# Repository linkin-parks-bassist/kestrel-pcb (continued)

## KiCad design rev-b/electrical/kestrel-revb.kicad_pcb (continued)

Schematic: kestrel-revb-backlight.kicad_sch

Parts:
C901: 4.7uF; C_0805_2012Metric; Rating 4.7uF / 25V X7R / input local
C902: 100nF; C_0603_1608Metric; Rating 100nF / 16V X7R / VIN bypass
C903: 2.2uF; C_1210_3225Metric; Rating 2.2uF / 50V X7R / effective >=1uF at 39V
C904: 100nF; C_0603_1608Metric; Rating 100nF / 16V X7R / buffer bypass
C905, C906: 4.7uF; C_0805_2012Metric; Rating 4.7uF / 16V X7R / effective >=1uF / LCD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
C907: 10pF; C_0603_1608Metric; Rating 10pF / 25V C0G / LCD feedforward
C908, C909: 4.7uF; C_0805_2012Metric; Rating 4.7uF / 16V X7R / effective >=1uF / tou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
C910: 10pF; C_0603_1608Metric; Rating 10pF / 25V C0G / touch feedforward
D901: SS16-E3/61T; D_SMA
L901: 10uH; L_Sunlord_MWSA0603S; Rating 10uH / shielded / Isat >=3A / MPN and l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
R901: 5.62ohm; R_0805_2012Metric; Rating 5.62ohm / 1% / >=0.125W / Kelvin sense
R902: 10k; R_0603_1608Metric; Rating 10k / 1% / MCU PWM default off
R903: 1k; R_0603_1608Metric; Rating 1k / 1% / control series
R904: 1M; R_1206_3216Metric; Rating 1M / 1% / 1206 / output bleed
R905: 100k; R_0603_1608Metric; Rating 100k / 1% / CTRL default off
R906: 33.2k; R_0603_1608Metric; Rating 33.2k / 0.1% / LCD upper feedback
R907: 10k; R_0603_1608Metric; Rating 10k / 0.1% / LCD lower feedback
R908: 30k; R_0603_1608Metric; Rating 30k / 0.1% / touch upper feedback
R909: 10k; R_0603_1608Metric; Rating 10k / 0.1% / touch lower feedback
TP901: BL_LED_A; TestPoint_Pad_D1.0mm
TP902: BL_LED_K; TestPoint_Pad_D1.0mm
TP903: LCD_VDD; TestPoint_Pad_D1.0mm
TP904: TOUCH_VDD; TestPoint_Pad_D1.0mm
U901: TPS61169DCKR; Texas_R-PDSO-G5_DCK-5
U902: SN74LVC1G125DCKR; Texas_R-PDSO-G5_DCK-5
U903, U904: TLV76701DRVR; WSON-6-1EP_2x2mm_P0.65mm_EP1x1.6mm_ThermalVias

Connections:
/+5V_DIG: C901.1, C902.1, C904.1, C905.1, C908.1, L901.1, U901.5 (VIN), U902.5 (VCC), U903.4 (EN), U903.6 (IN), U904.4 (EN), U904.6 (IN); also elsewhere on the board
/BL_LED_A: C903.1, D901.1 (K), R904.1, TP901.1; also elsewhere on the board
/BL_LED_K: R901.1, TP902.1, U901.3 (FB); also elsewhere on the board
/Backlight and display supplies/BL_CTRL: R903.2, R905.1, U901.4 (CTRL)
/Backlight and display supplies/BL_CTRL_BUFFER: R903.1, U902.4
/Backlight and display supplies/BL_SW: D901.2 (A), L901.2, U901.1 (SW)
/Backlight and display supplies/LCD_FB: C907.2, R906.2, R907.1, U903.2 (FB)
/Backlight and display supplies/TOUCH_FB: C910.2, R908.2, R909.1, U904.2 (FB)
/GND: C901.2, C902.2, C903.2, C904.2, C905.2, C906.2, C908.2, C909.2, R901.2, R902.2, R904.2, R905.2, R907.2, R909.2, U901.2 (GND), U902.1, U902.3 (GND), U903.3 (GND), U903.5 (GND), U903.7 (PAD), U904.3 (GND), U904.5 (GND), U904.7 (PAD); also elsewhere on the board
/LCD_VDD: C906.1, C907.1, R906.1, TP903.1, U903.1 (OUT); also elsewhere on the board
/MCU_BL_PWM: R902.1, U902.2; also elsewhere on the board
/TOUCH_VDD: C909.1, C910.1, R908.1, TP904.1, U904.1 (OUT); also elsewhere on the board

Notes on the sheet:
ONBOARD BACKLIGHT BOOST - REFERENCE PANEL - ENGINEERING DRAFT
GPIO8 PWM defaults low. Use 5-100kHz; buffered on 5V domain with Ioff; controlled by firmware.
5.62ohm sets 36.30mA nominal / <=39.55mA conditional TA>=25C limits. Cold-temperature regulation remains to qualify.
J1001: pin2 anode / pin1 cathode. Never ground LED cathode; Kelvin route to FB and R901.
Disabled boost retains VIN-to-output passive path. Panel Vf must exceed VIN; no hard output disconnect or hot-plug claim.
LCD and touch supplies onboard. Panel contact orientation, exact parts/effective capacitance and qualification pending.
LCD LOGIC: TLV76701 / 33.2k:10k 0.1% / 3.456V nominal. Conditional DC corners 3.414..3.498V; not touch VDD.
Panel VDD 3.3..3.6V. 5V source headroom, load/thermal, effective capacitors, bus levels and ramp/backfeed require qualification.
TI adjustable DRV pins: 1 OUT, 2 FB, 3/5/EP GND, 4 EN, 6 IN. TP903 probes LCD power; J1001 is the LCD connector.
TOUCH: 30k:10k 0.1% / 3.2V nominal. GT911 recommended supply max3.3V, absolute max3.47V. Do not use LCD_VDD.
Touch load, exact capacitors, reset/address timing, rail-ramp/backfeed and GPIO/I2C behavior require qualification.

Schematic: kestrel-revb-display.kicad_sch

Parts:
C1001, C1002, C1003, C1004: 100nF; C_0603_1608Metric; Rating 100nF / 16V X7R / FPC supply bypass
J1001: LCD RGB / contact fit pending; Hirose_FH12-40S-0.5SH_1x40-1MP_P0.50mm_Horizontal
J1002: CAP TOUCH / contact fit pending; Hirose_FH12-8S-0.5SH_1x08-1MP_P0.50mm_Horizontal
R1001, R1002, R1003, R1004, R1005, R1006, R1007, R1008, R1009, R1010, R1011, R1012, R1013, R1014, R1015, R1016: 33ohm; R_0402_1005Metric; Rating 33ohm / 1% / 0.063W at 70C / 50V limiti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; MPN RC0402FR-0733RL; LCSC C138002
R1017, R1018, R1019, R1020, R1021, R1022, R1023, R1024, R1025: 33ohm; R_0603_1608Metric; Rating 33ohm / 1% / GPIO source damping starti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
R1026, R1027: 4.7k; R_0603_1608Metric; Rating 4.7k / 1% / I2C pullup to touch rail
R1028, R1029: 10k; R_0603_1608Metric; Rating 10k / 1% / default low
R1030: 100k; R_0603_1608Metric; Rating 100k / 1% / default low

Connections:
/BL_LED_A: J1001.2; also elsewhere on the board
/BL_LED_K: J1001.1; also elsewhere on the board
/GND: C1001.2, C1002.2, C1003.2, C1004.2, J1001.3, J1001.5, J1001.6, J1001.7, J1001.13, J1001.14, J1001.21, J1001.22, J1001.23, J1001.29, J1001.36, J1002.1, J1002.8, R1028.2, R1029.2, R1030.2; also elsewhere on the board
/LCD_VDD: C1001.1, C1002.1, J1001.4; also elsewhere on the board
/MCU_LCD_B3: R1001.1; also elsewhere on the board
/MCU_LCD_B4: R1002.1; also elsewhere on the board
/MCU_LCD_B5: R1003.1; also elsewhere on the board
/MCU_LCD_B6: R1004.1; also elsewhere on the board
/MCU_LCD_B7: R1005.1; also elsewhere on the board
/MCU_LCD_DE: R1020.1; also elsewhere on the board
/MCU_LCD_DISP: R1021.1; also elsewhere on the board
/MCU_LCD_G2: R1006.1; also elsewhere on the board
/MCU_LCD_G3: R1007.1; also elsewhere on the board
/MCU_LCD_G4: R1008.1; also elsewhere on the board
/MCU_LCD_G5: R1009.1; also elsewhere on the board
/MCU_LCD_G6: R1010.1; also elsewhere on the board
/MCU_LCD_G7: R1011.1; also elsewhere on the board
/MCU_LCD_HSYNC: R1018.1; also elsewhere on the board
/MCU_LCD_PCLK: R1017.1; also elsewhere on the board
/MCU_LCD_R3: R1012.1; also elsewhere on the board
/MCU_LCD_R4: R1013.1; also elsewhere on the board
/MCU_LCD_R5: R1014.1; also elsewhere on the board
/MCU_LCD_R6: R1015.1; also elsewhere on the board
/MCU_LCD_R7: R1016.1; also elsewhere on the board
/MCU_LCD_VSYNC: R1019.1; also elsewhere on the board
/MCU_TOUCH_INT: R1024.1; also elsewhere on the board
/MCU_TOUCH_RST_N: R1025.1; also elsewhere on the board
/MCU_TOUCH_SCL: R1022.1; also elsewhere on the board
/MCU_TOUCH_SDA: R1023.1; also elsewhere on the board
/RGB565 and capacitive touch/LCD_B3: J1001.24, R1001.2
/RGB565 and capacitive touch/LCD_B4: J1001.25, R1002.2
/RGB565 and capacitive touch/LCD_B5: J1001.26, R1003.2
/RGB565 and capacitive touch/LCD_B6: J1001.27, R1004.2
/RGB565 and capacitive touch/LCD_B7: J1001.28, R1005.2
/RGB565 and capacitive touch/LCD_DE: J1001.34, R1020.2
/RGB565 and capacitive touch/LCD_DISP: J1001.31, R1021.2, R1028.1
/RGB565 and capacitive touch/LCD_G2: J1001.15, R1006.2
/RGB565 and capacitive touch/LCD_G3: J1001.16, R1007.2
/RGB565 and capacitive touch/LCD_G4: J1001.17, R1008.2
/RGB565 and capacitive touch/LCD_G5: J1001.18, R1009.2
/RGB565 and capacitive touch/LCD_G6: J1001.19, R1010.2
/RGB565 and capacitive touch/LCD_G7: J1001.20, R1011.2
/RGB565 and capacitive touch/LCD_HSYNC: J1001.32, R1018.2
/RGB565 and capacitive touch/LCD_PCLK: J1001.30, R1017.2
/RGB565 and capacitive touch/LCD_R3: J1001.8, R1012.2
/RGB565 and capacitive touch/LCD_R4: J1001.9, R1013.2
/RGB565 and capacitive touch/LCD_R5: J1001.10, R1014.2
/RGB565 and capacitive touch/LCD_R6: J1001.11, R1015.2
/RGB565 and capacitive touch/LCD_R7: J1001.12, R1016.2
/RGB565 and capacitive touch/LCD_VSYNC: J1001.33, R1019.2
/RGB565 and capacitive touch/TOUCH_INT: J1002.6, R1024.2, R1030.1
/RGB565 and capacitive touch/TOUCH_RST_N: J1002.7, R1025.2, R1029.1
/RGB565 and capacitive touch/TOUCH_SCL: J1002.4, R1022.2, R1026.2
/RGB565 and capacitive touch/TOUCH_SDA: J1002.5, R1023.2, R1027.2
/TOUCH_VDD: C1003.1, C1004.1, J1002.2, J1002.3, R1026.1, R1027.1; also elsewhere on the board

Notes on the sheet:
RGB565 / CAPACITIVE TOUCH - DM-TFT50-404 REFERENCE - ENGINEERING DRAFT
RGB565: GPIO39/40/41/42/43 -> B3..7; GPIO44/45/46/47/32/49 -> G2..7; GPIO26/27/28/33/30 -> R3..7. Low panel data bits grounded.
GPIO9 PCLK / 10 HSYNC / 11 VSYNC / 12 DE / 13 DISP. GPIO15 SCL / 16 SDA / 17 INT / 18 RESET.
LCD power 3.456V; GT911 VDD/VDDIO 3.2V. 4.7k I2C pullups to TOUCH_VDD. INT is bidirectional during reset/address selection.
FPC contact side/numbering/thickness, exact parts, loaded signal timing, reset/address sequence and power-off/backfeed pending.
R1001..R1025 are source-damping starting values; place appropriately near drivers. No external hot-plug or EMC rating established.

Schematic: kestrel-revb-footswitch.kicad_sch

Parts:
C1101, C1103: 100nF; C_0603_1608Metric; Rating 100nF / 16V X7R / RC filter / effective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
C1102, C1104: 100nF; C_0603_1608Metric; Rating 100nF / 16V X7R / buffer bypass
D1101, D1102: PESD5V0U1BA,115; D_SOD-323
J1101, J1102: FOOT WIRE: 1SIGNAL 2GND; SolderWire-0.127sqmm_1x02_P3.7mm_D0.48mm_OD1mm_Relief2x
R1101, R1104: 1k; R_0603_1608Metric; Rating 1k / 1% / wire input series
R1102, R1105: 10k; R_0603_1608Metric; Rating 10k / 1% / input pullup
R1103, R1106: 33ohm; R_0603_1608Metric; Rating 33ohm / 1% / GPIO source damping
SW1101, SW1102: SWFS0013 / silent momentary NO / candidate
U1101, U1102: SN74LVC1G17DCKR; Texas_R-PDSO-G5_DCK-5

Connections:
/+3V3_D: C1102.1, C1104.1, R1102.1, R1105.1, U1101.5 (VCC), U1102.5 (VCC); also elsewhere on the board
/GND: C1101.2, C1102.2, C1103.2, C1104.2, D1101.2 (A2), D1102.2 (A2), J1101.2, J1102.2, SW1101.2, SW1102.2, U1101.3 (GND), U1102.3 (GND); also elsewhere on the board
/MCU_FOOT0_N: R1103.2; also elsewhere on the board
/MCU_FOOT1_N: R1106.2; also elsewhere on the board
/Two momentary footswitch inputs/FOOT_BUF_0: R1103.1, U1101.4
/Two momentary footswitch inputs/FOOT_BUF_1: R1106.1, U1102.4
/Two momentary footswitch inputs/FOOT_RAW_0: D1101.1 (A1), J1101.1, R1101.1, SW1101.1
/Two momentary footswitch inputs/FOOT_RAW_1: D1102.1 (A1), J1102.1, R1104.1, SW1102.1
/Two momentary footswitch inputs/FOOT_RC_0: C1101.1, R1101.2, R1102.2, U1101.2
/Two momentary footswitch inputs/FOOT_RC_1: C1103.1, R1104.2, R1105.2, U1102.2

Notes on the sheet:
TWO PANEL-MOUNT MOMENTARY FOOTSWITCHES - ACTIVE LOW - ENGINEERING DRAFT
GPIO20 pad22 = left / GPIO21 pad23 = right. Switches close signal to ground; mount loads on enclosure, not PCB.
10k pullup / 1k series / 100nF RC / Schmitt buffer. Short interference filtering is not complete contact debounce.
SWFS0013 is a local A$5 silent SPST candidate: manufacturer/current rating, dry-contact life and exact geometry unqualified.
PESD wire shunts do not establish system ESD/fault rating. Qualify residual stress, firmware edges, wiring and physical loads.

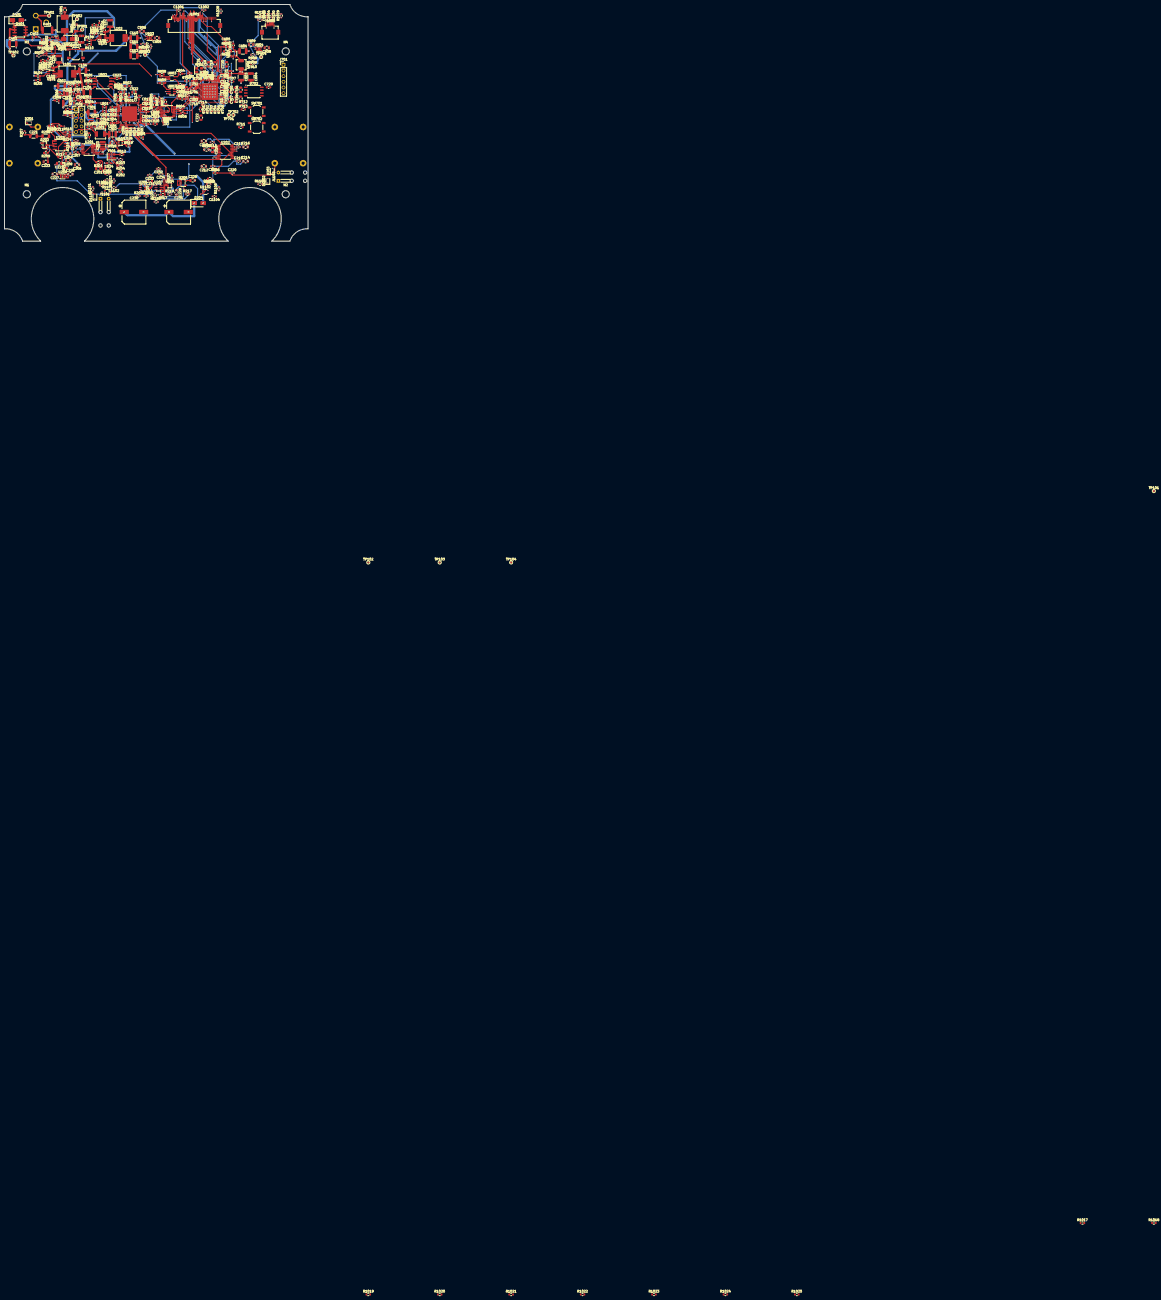
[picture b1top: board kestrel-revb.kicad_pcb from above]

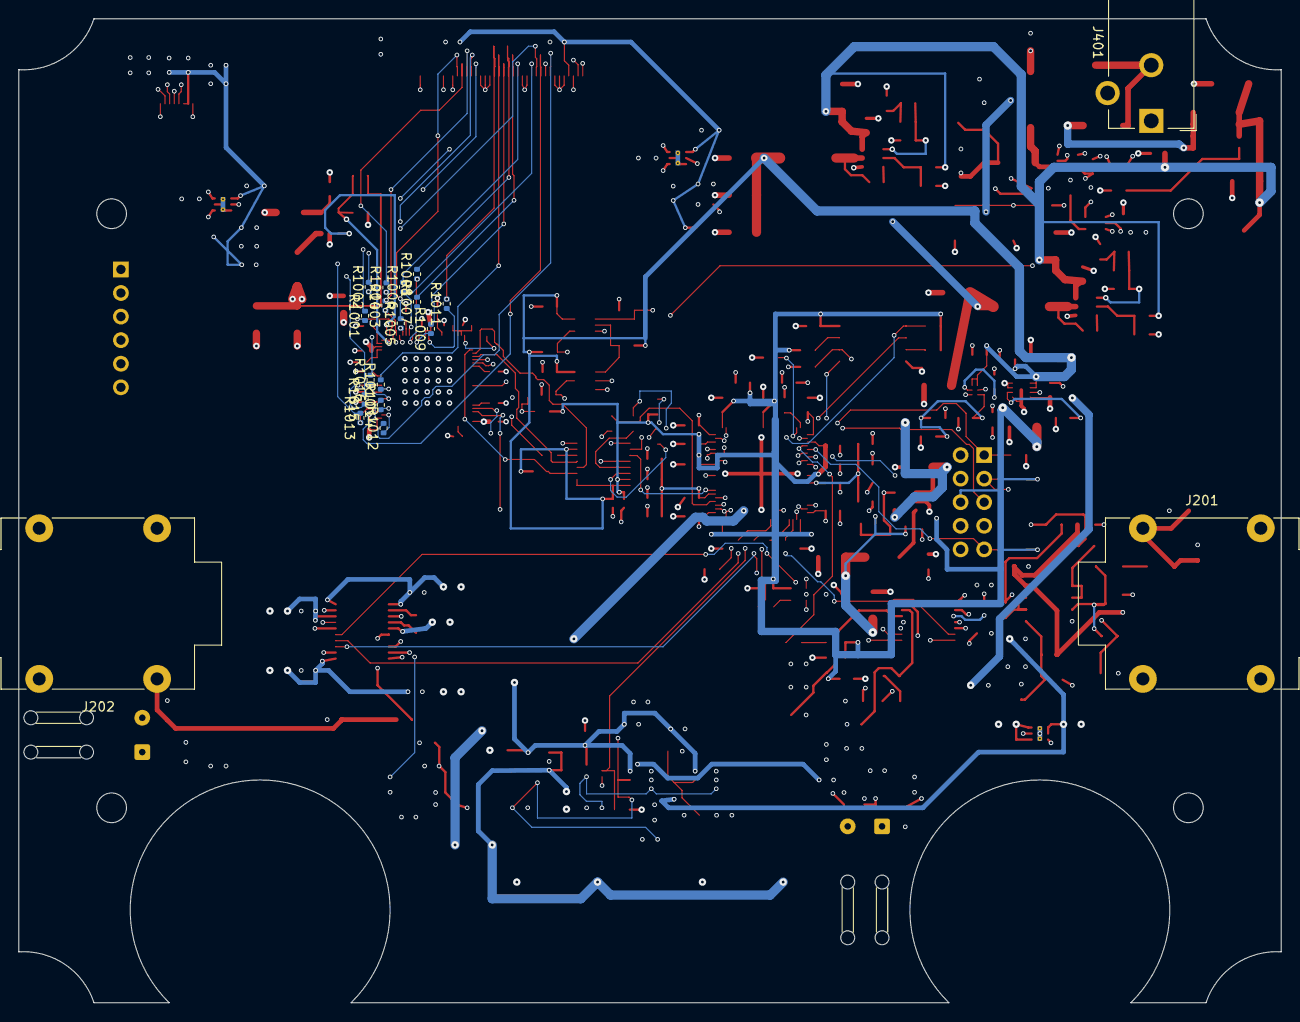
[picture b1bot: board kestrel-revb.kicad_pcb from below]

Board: 4 copper layers, 136.0 x 106.0 mm, 351 parts (19 on the bottom side), 199 nets.

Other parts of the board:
H1, H2, H3, H4: MountingHole_3.2mm_M3

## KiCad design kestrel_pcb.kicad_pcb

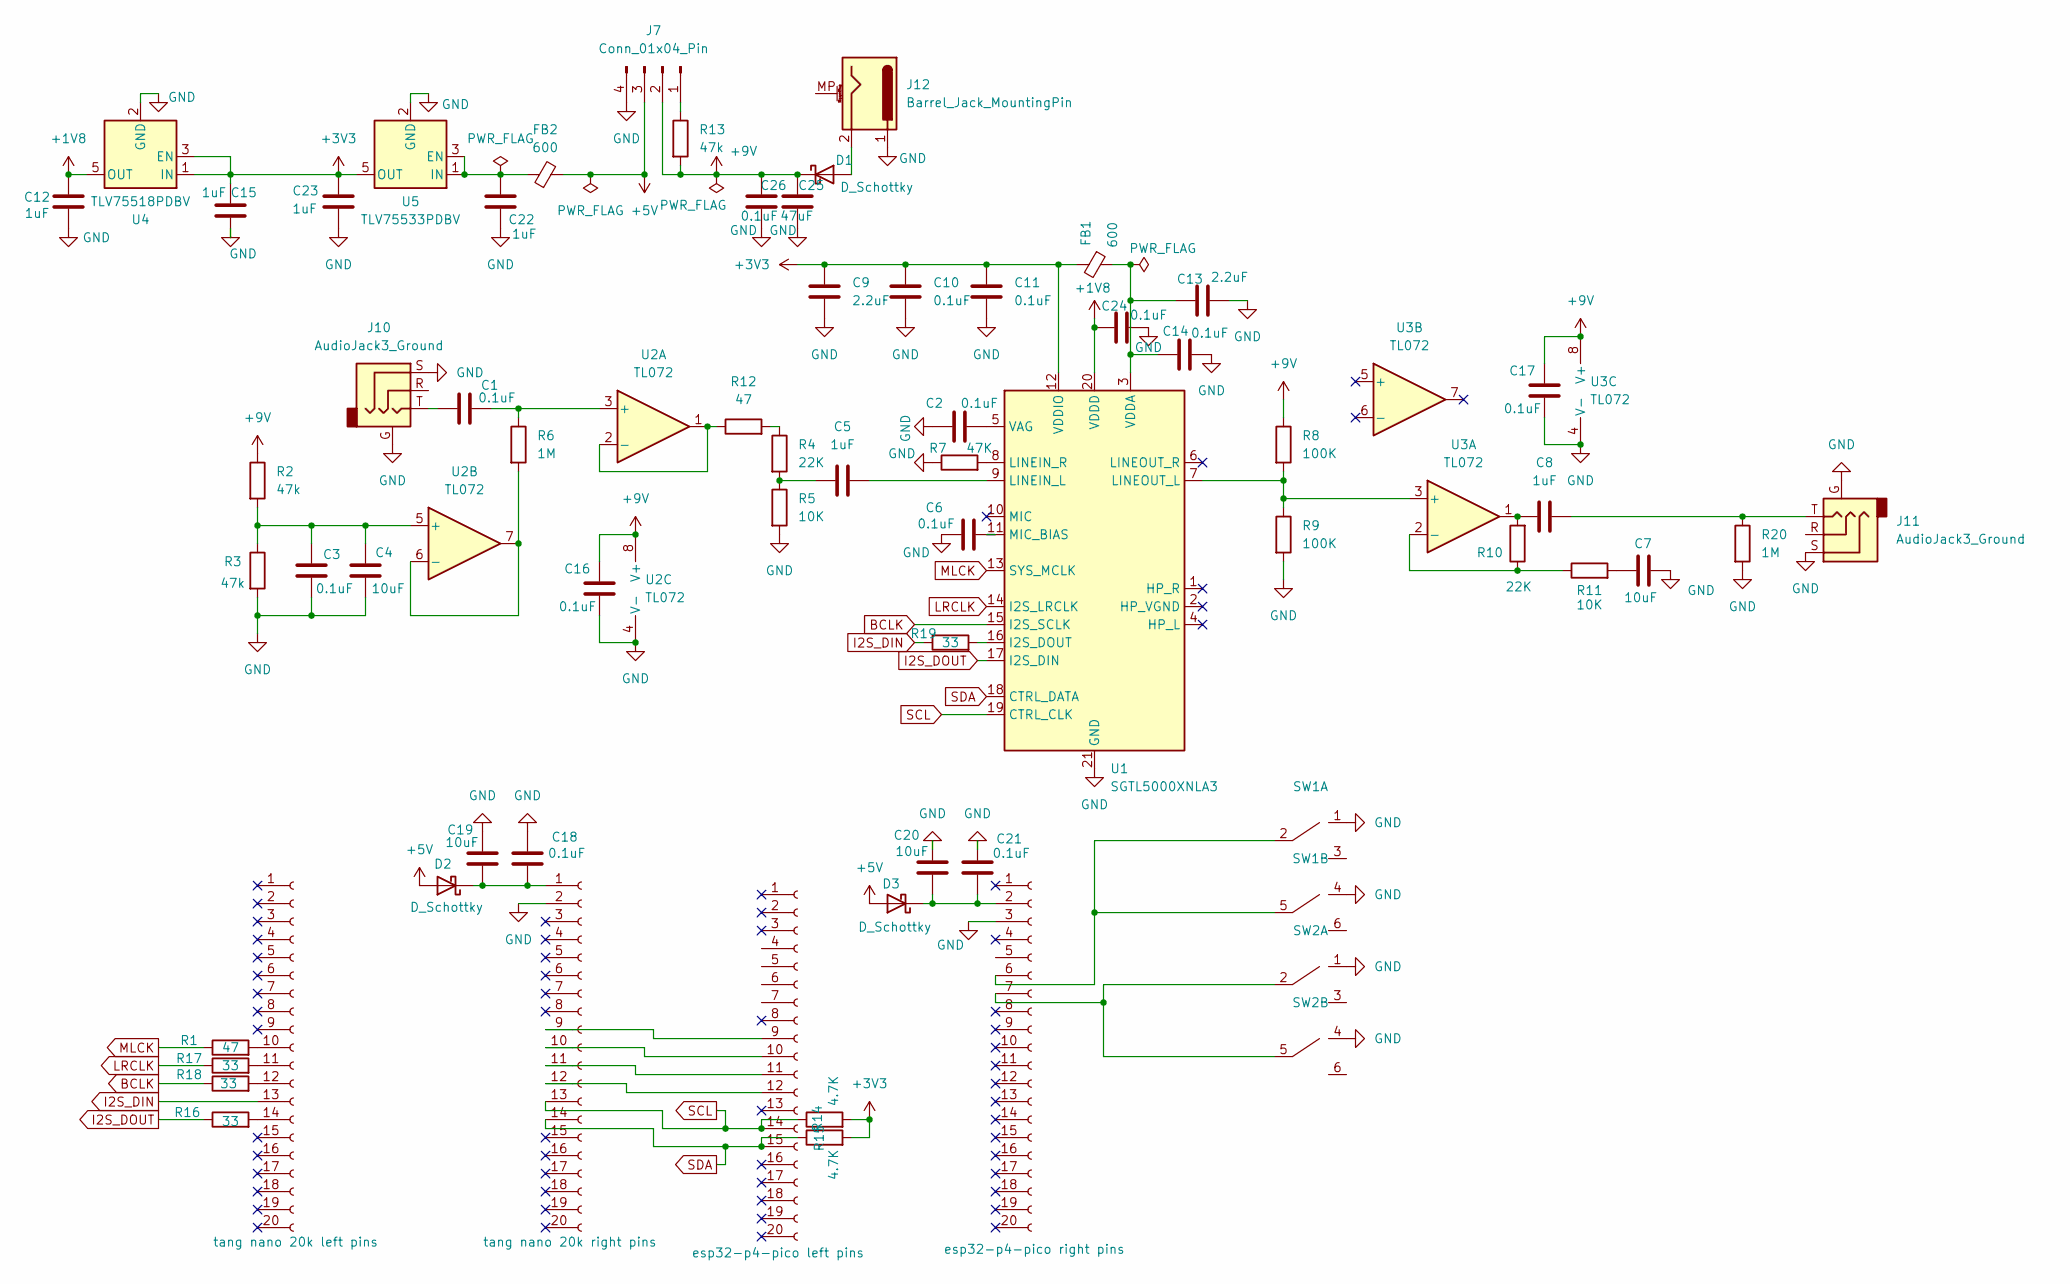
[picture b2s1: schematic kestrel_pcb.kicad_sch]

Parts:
C1, C2, C3, C6, C10, C11, C14, C16, C17, C18, C21, C24, C26: 0.1uF; C_0603_1608Metric; LCSC C14663
C4, C7, C19, C20: 10uF; C_0603_1608Metric; LCSC C19702
C5, C8, C12, C15, C22, C23: 1uF; C_0603_1608Metric; LCSC C15849
C9, C13: 2.2uF; C_0603_1608Metric; LCSC C23630
C25: 47uF; C_0603_1608Metric; LCSC C1622
D1, D2, D3: D_Schottky; D_0603_1608Metric; LCSC C3312582
FB1, FB2: 600; L_0603_1608Metric; LCSC C48543396
J1: tang nano 20k left pins; PinSocket_1x20_P2.54mm_Vertical
J2: tang nano 20k right pins; PinSocket_1x20_P2.54mm_Vertical
J3: esp32-p4-pico left pins; PinSocket_1x20_P2.54mm_Vertical
J4: esp32-p4-pico right pins; PinSocket_1x20_P2.54mm_Vertical
J7: Conn_01x04_Pin; PinSocket_1x04_P2.54mm_Vertical
J10, J11: AudioJack3_Ground; Jack_6.35mm_Neutrik_NMJ4HCD2_Horizontal
J12: Barrel_Jack_MountingPin; BarrelJack_Horizontal
R1, R12: 47; R_0603_1608Metric; LCSC C114623
R2, R3, R13: 47k; R_0603_1608Metric; LCSC C105579
R4, R10: 22K; R_0603_1608Metric; LCSC C114065
R5, R11: 10K; R_0603_1608Metric; LCSC C98220
R6, R20: 1M; R_0603_1608Metric; LCSC C105578
R7: 47K; R_0603_1608Metric; LCSC C105579
R8, R9: 100K; R_0603_1608Metric; LCSC C14675
R14, R15: 4.7K; R_0603_1608Metric; LCSC C99782
R16, R17, R18, R19: 33; R_0603_1608Metric; LCSC C2909394
SW1, SW2: Switch_3PDT
U1: SGTL5000XNLA3; QFN-20-1EP_3x3mm_P0.4mm_EP1.65x1.65mm; LCSC C2802658
U2, U3: TL072; DIP-8_W7.62mm
U4: TLV75518PDBV; SOT-23-5; LCSC C2877863
U5: TLV75533PDBV; SOT-23-5; LCSC C404027

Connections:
+1V8: C12.1, C24.1, U1.20 (VDDD), U4.5 (OUT)
+3V3: C9.1, C10.1, C11.1, C15.1, C23.1, FB1.2, R14.2, R15.2, U1.12 (VDDIO), U4.1 (IN), U4.3 (EN), U5.5 (OUT)
+5V: D2.2 (A), D3.2 (A), FB2.2, J7.3; also elsewhere on the board
+9V: C16.1, C17.1, C25.1, C26.1, D1.1 (K), J7.2, R2.1, R8.1, R13.2, U2.8 (V+), U3.8 (V+); also elsewhere on the board
BCLK: R18.1, U1.15 (I2S_SCLK)
GND: C2.1, C3.2, C4.2, C6.1, C7.2, C9.2, C10.2, C11.2, C12.2, C13.1, C14.2, C15.2, C16.2, C17.2, C18.1, C19.1, C20.1, C21.1, C22.2, C23.2, C24.2, C25.2, C26.2, J2.2, J4.3, J7.4, J10.G, J10.S, J11.G, J11.S, J12.1, R3.2, R5.2, R7.1, R9.2, R20.2, SW1.1, SW1.4, SW2.1, SW2.4, U1.21 (GND), U2.4 (V-), U3.4 (V-), U4.2 (GND), U5.2 (GND); also elsewhere on the board
I2S_DIN: J1.13, R19.1
I2S_DOUT: R16.1, U1.17 (I2S_DIN)
LRCLK: R17.1, U1.14 (I2S_LRCLK)
MLCK: R1.1, U1.13 (SYS_MCLK)
unnamed: C1.1, J10.T
unnamed: C5.1, R4.2, R5.1
unnamed: C7.1, R11.2
unnamed: C8.1, R10.2, U3.1
unnamed: C8.2, J11.T, R20.1
unnamed: D1.2 (A), J12.2
unnamed: C18.2, C19.2, D2.1 (K), J2.1
unnamed: C20.2, C21.2, D3.1 (K), J4.2
unnamed: J1.10, R1.2
unnamed: J1.11, R17.2
unnamed: J1.12, R18.2
unnamed: J1.14, R16.2
unnamed: J2.9, J3.9
unnamed: J2.10, J3.10
unnamed: J2.11, J3.11
unnamed: J2.12, J3.12
unnamed: J4.6, SW1.2, SW1.5
unnamed: J4.7, SW2.2, SW2.5
unnamed 28: J7.1, R13.1; also elsewhere on the board
unnamed: R4.1, R12.2
unnamed: R19.2, U1.16 (I2S_DOUT)
unnamed: C5.2, U1.9 (LINEIN_L)
unnamed: R7.2, U1.8 (LINEIN_R)
unnamed: R8.2, R9.1, U1.7 (LINEOUT_L), U3.3 (+)
unnamed: C6.2, U1.11 (MIC_BIAS)
unnamed: C2.2, U1.5 (VAG)
unnamed: C13.2, C14.1, FB1.1, U1.3 (VDDA)
unnamed: C1.2, R6.1, U2.3 (+)
unnamed: R12.1, U2.1, U2.2 (-)
unnamed: C3.1, C4.1, R2.2, R3.1, U2.5 (+)
unnamed: R6.2, U2.6 (-), U2.7
unnamed: R10.1, R11.1, U3.2 (-)
unnamed: C22.1, FB2.1, U5.1 (IN), U5.3 (EN)
SCL: J2.13, J3.14, R14.1, U1.19 (CTRL_CLK)
SDA: J2.14, J3.15, R15.1, U1.18 (CTRL_DATA)

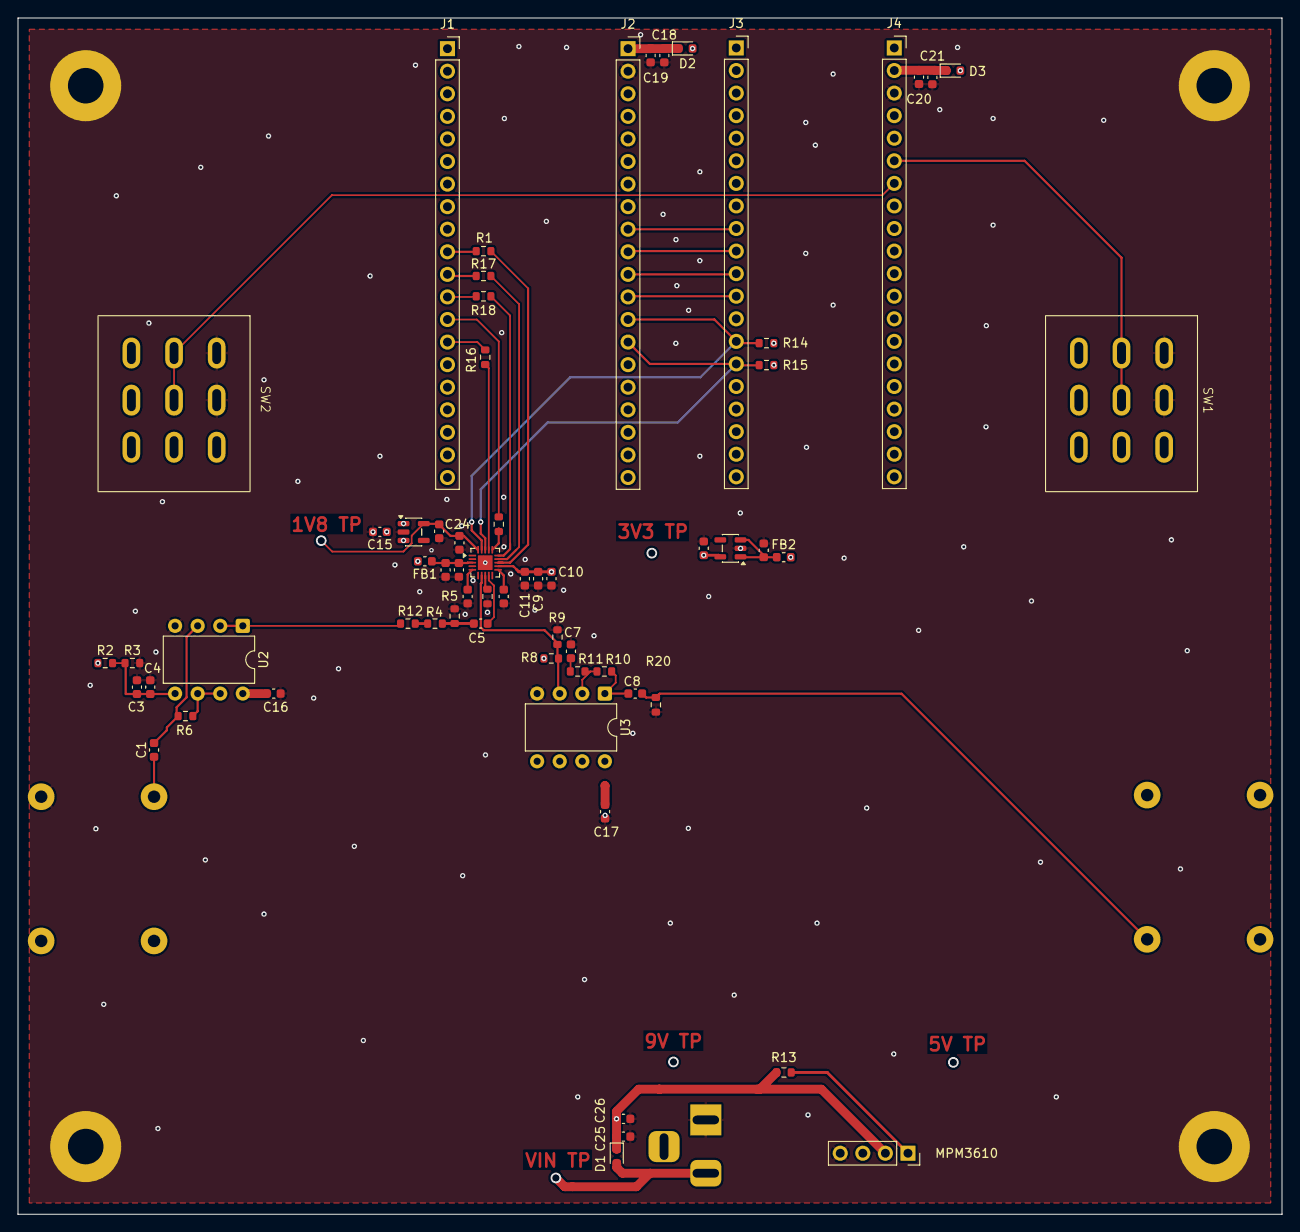
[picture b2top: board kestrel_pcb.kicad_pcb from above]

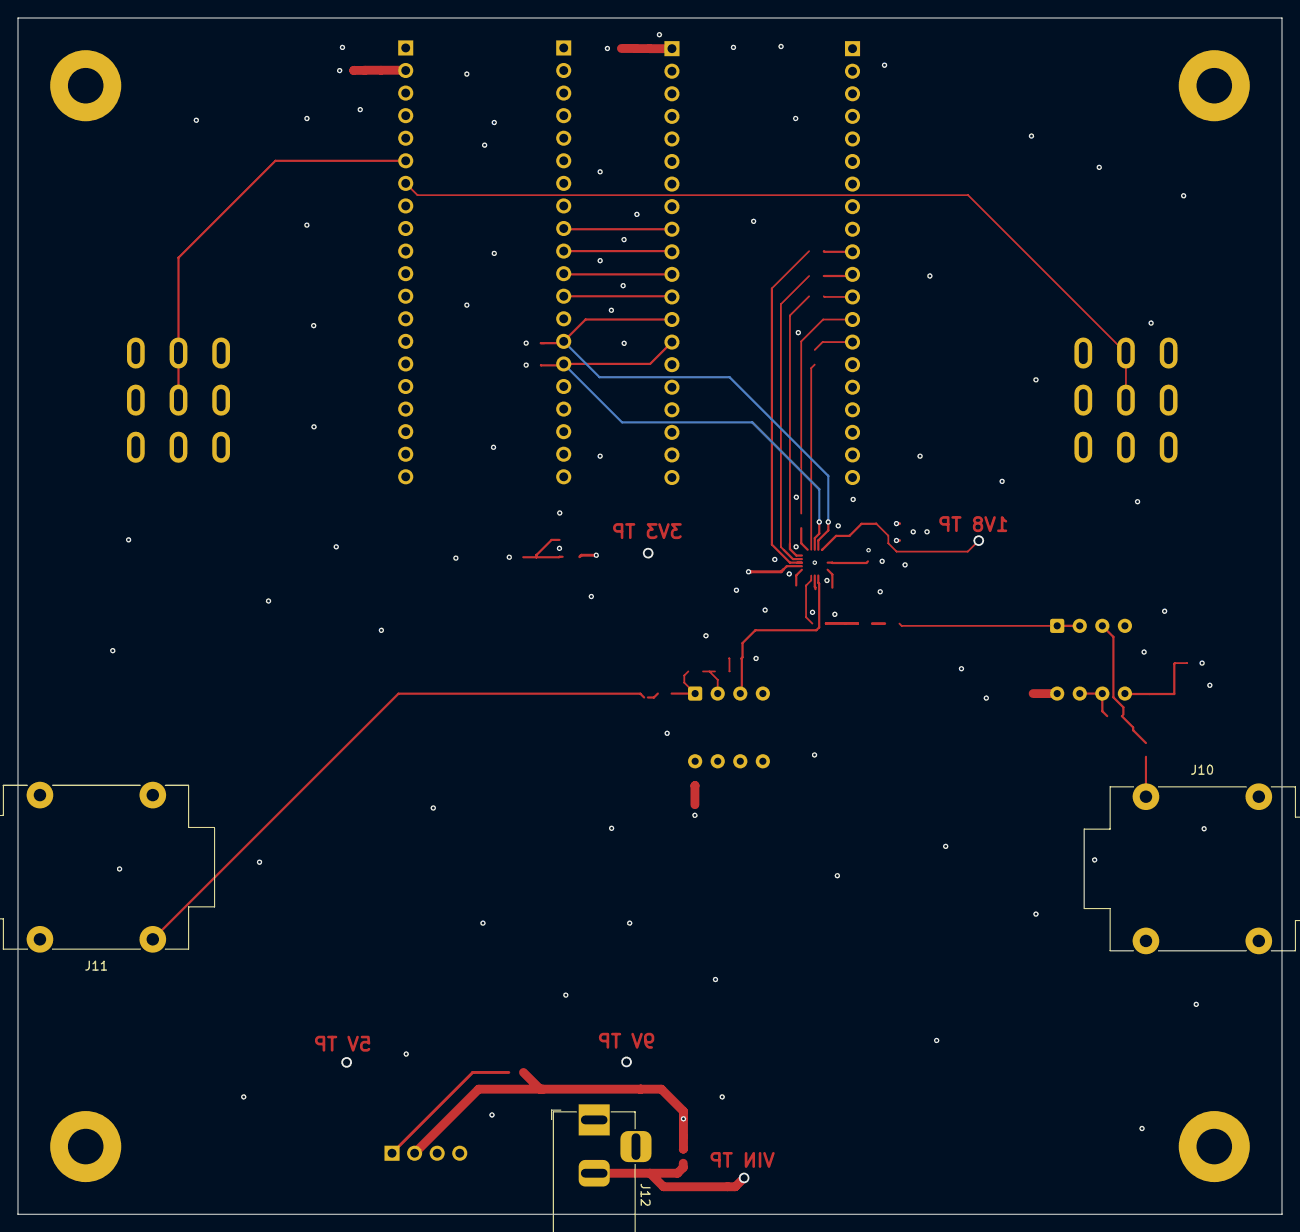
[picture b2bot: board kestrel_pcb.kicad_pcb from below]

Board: 4 copper layers, 142.2 x 134.6 mm, 66 parts (3 on the bottom side), 45 nets.

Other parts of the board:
MPM3610: Conn_01x04_Pin; PinSocket_1x04_P2.54mm_Vertical

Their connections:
+5V: MPM3610.3; also elsewhere on the board
+9V: MPM3610.2; also elsewhere on the board
GND: MPM3610.4; also elsewhere on the board
unnamed 28: MPM3610.1; also elsewhere on the board

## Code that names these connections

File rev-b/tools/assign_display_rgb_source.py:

#!/usr/bin/env python3
"""Guarded, pairwise remap of six RGB data bits to free right-side GPIOs."""
import argparse
import xml.etree.ElementTree as ET
from pathlib import Path
import pcbnew
ROOT=Path(__file__).resolve().parents[1]
def main():
 p=argparse.ArgumentParser();p.add_argument('--board',type=Path);p.add_argument('--trial-output',type=Path);args=p.parse_args();path=ROOT/'electrical/kestrel-revb.kicad_pcb';b=pcbnew.LoadBoard(str(args.board or path));f=next(f for f in b.GetFootprints()if f.GetReference()=='U701');pads={p.GetNumber():p for p in f.Pads()};xml=ET.parse(ROOT/'generated/revb-netlist.xml');expected={node.attrib['pin']:n.attrib['name']for n in xml.findall('.//nets/net')for node in n.findall('node')if node.attrib['ref']=='U701'}
 old={'55':'unconnected-(U701C-GPIO26-Pad55)','93':'/MCU_LCD_R3','57':'unconnected-(U701C-GPIO28-Pad57)','95':'/MCU_LCD_R5','60':'unconnected-(U701C-GPIO30-Pad60)','98':'/MCU_LCD_R7','63':'unconnected-(U701C-GPIO32-Pad63)','90':'/MCU_LCD_G6'}
 old.update({'56':'unconnected-(U701C-GPIO27-Pad56)','94':'/MCU_LCD_R4','64':'unconnected-(U701D-GPIO33-Pad64)','97':'/MCU_LCD_R6'})
 assert {n:expected[n]for n in old}=={'55':'/MCU_LCD_R3','93':'unconnected-(U701E-GPIO50-Pad93)','57':'/MCU_LCD_R5','95':'unconnected-(U701E-GPIO52-Pad95)','60':'/MCU_LCD_R7','98':'unconnected-(U701E-GPIO54-Pad98)','63':'/MCU_LCD_G6','90':'unconnected-(U701D-GPIO48-Pad90)','56':'/MCU_LCD_R4','94':'unconnected-(U701E-GPIO51-Pad94)','64':'/MCU_LCD_R6','97':'unconnected-(U701E-GPIO53-Pad97)'}
 conn=b.GetConnectivity();conn.Build(b)
 changed=[]
 for pair in [('55','93'),('57','95'),('60','98'),('63','90'),('56','94'),('64','97')]:
  if all(pads[n].GetNetname()==expected[n]for n in pair):continue
  for n in pair:
   assert pads[n].GetNetname()==old[n],n
   assert all(x.m_Uuid.AsString()==pads[n].m_Uuid.AsString()for x in conn.GetConnectedItems(pads[n])),f'Pad{n} already routed'
  changed.extend(pair)
 if not changed:print('Verified current RGB GPIO26/27/28/30/32/33 allocation');return
 for n in changed:
  net=b.FindNet(expected[n])
  if net is None:net=pcbnew.NETINFO_ITEM(b,expected[n]);b.Add(net)
  pads[n].SetNet(net)
 b.RemoveUnusedNets(None);pcbnew.SaveBoard(str(args.trial_output or path),b);print(f'Assigned current RGB GPIO26/27/28/30/32/33 allocation; {len(changed)} unrouted pad nets changed')
if __name__=='__main__':main()

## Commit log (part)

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2026-03-13 Add files
2026-03-13 Update board, readme, image
2026-03-20 Fix files, new image, add 3d models, fix board-sides
